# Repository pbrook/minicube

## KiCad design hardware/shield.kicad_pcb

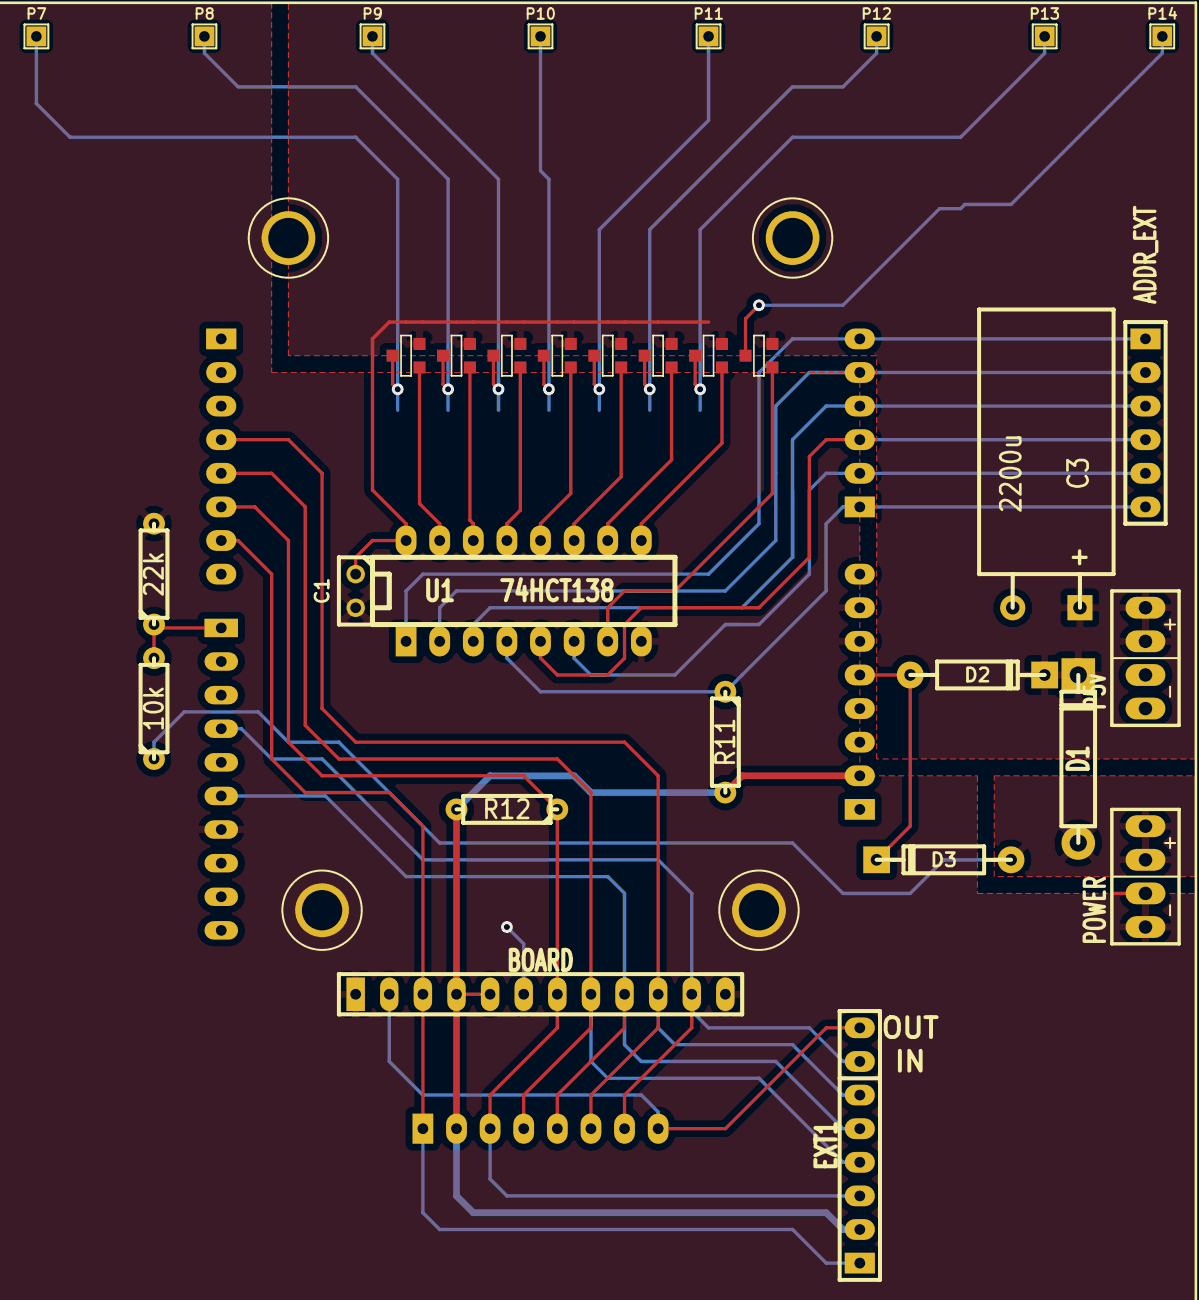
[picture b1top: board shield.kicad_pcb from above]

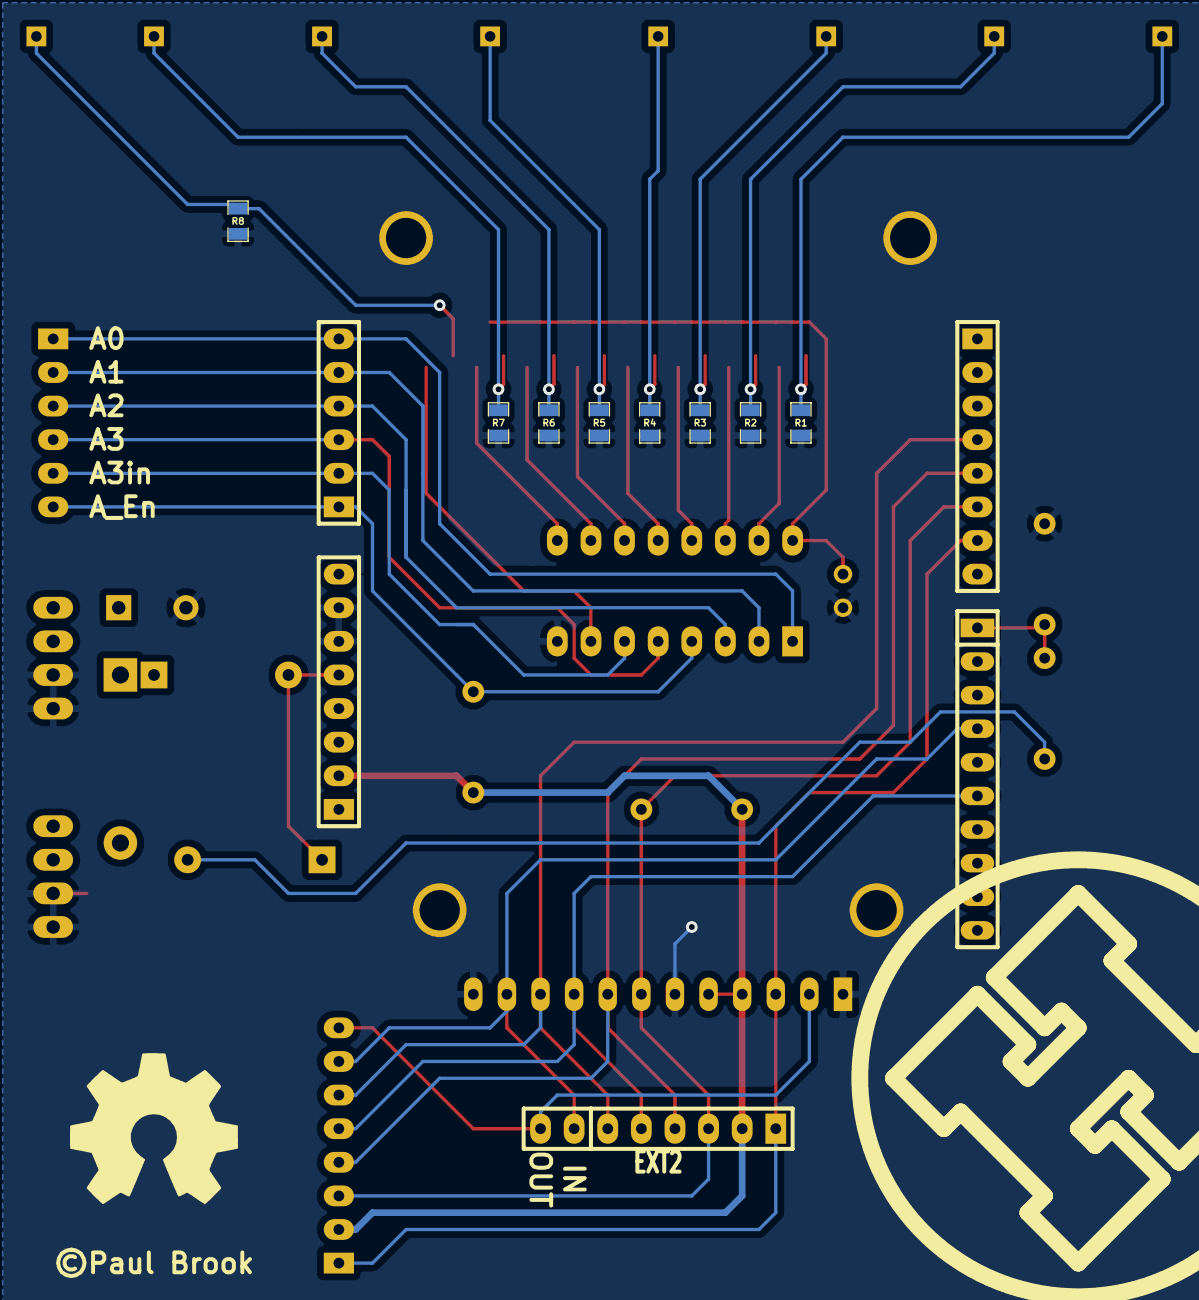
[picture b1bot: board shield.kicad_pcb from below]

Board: 2 copper layers, 49 parts (14 on the bottom side), 35 nets.

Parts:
C1: 100n; C1
C3: 2200u; CPR10X20
D1: DIODESCH; D5
D2: DIODESCH; DO-41
D3: DIODE; DO-41
HACKSPACE_LOGO: VAL**; HACKSPACE_LOGO
P1: D0_7; SIL-8-ELL
P2: D8_13; SIL-10-ELL
P3: POWER; SIL-8-ELL
P4: A0_5; SIL-6-ELL
P5: POWER; power2
P6: BOARD; SIL-12-ELL
P7, P8, P9, P10, P11, P12, P13, P14: CONN_1; SIL-1
P15, P16, P17, P18: CONN_1; HOLE3
P19: P5v; power2
P20: EXT1; SIL-8-ELL
P21: ADDR_EXT; SIL-6-ELL
P22: EXT2; SIL-8-ELL
Q1, Q2, Q3, Q4, Q5, Q6, Q7, Q8: MOS_P; SOT23GDS_NP
R1, R2, R3, R4, R5, R6, R7, R8: R; 0805
R9: 10k; R3-LARGE_PADS
R10: 22k; R3-LARGE_PADS
R11, R12: R; R3-LARGE_PADS
U1: 74HCT138; DIP-16__300_ELL

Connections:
/5v: C1.1, C3.1, D1.2, D2.2, P19.2, Q1.S, Q2.S, Q3.S, Q4.S, Q5.S, Q6.S, Q7.S, Q8.S, U1.16
/5v_EXT: D1.1, D3.1, P5.2, R9.1
/5v_USB: D2.1, D3.2, P3.5
/A0: P4.6, P21.1, U1.1
/A1: P4.5, P21.2, U1.2
/A2: P4.4, P21.3, U1.3
/A3: P4.3, P21.4, U1.5
/A3in: P4.2, P21.5, U1.6
/A_EN: P4.1, P21.6, R11.1, U1.4
/BLANK: P1.6, P6.7, P20.3, P22.3, R12.1
/GND: C1.2, C3.2, P2.7, P3.6, P3.7, P5.1, P6.1, P6.6, P6.12, P15.1, P16.1, P17.1, P18.1, P19.1, R1.2, R2.2, R3.2, R4.2, R5.2, R6.2, R7.2, R8.2, R10.2, U1.8
/GSCLK: P1.7, P6.3, P20.1, P22.1
/MODE: P1.4, P6.10, P20.6, P22.6
/Q1: Q1.G, U1.15
/Q2: Q2.G, U1.14
/Q3: Q3.G, U1.13
/Q4: Q4.G, U1.12
/Q5: Q5.G, U1.11
/Q6: Q6.G, U1.10
/Q7: Q7.G, U1.9
/Q8: Q8.G, U1.7
/S1: P7.1, Q1.D, R1.1
/S2: P8.1, Q2.D, R2.1
/S3: P9.1, Q3.D, R3.1
/S4: P10.1, Q4.D, R4.1
/S5: P11.1, Q5.D, R5.1
/S6: P12.1, Q6.D, R6.1
/S7: P13.1, Q7.D, R7.1
/S8: P14.1, Q8.D, R8.1
/SCLK: P2.6, P6.9, P20.5, P22.5
/SENSE_EXT: P2.1, R9.2, R10.1
/SIN: P2.4, P6.11, P20.7, P22.7
/SOUT: P6.2, P20.8, P22.8
/VCC: P3.2, P6.4, P6.5, P20.2, P22.2, R11.2, R12.2
/XLAT: P1.5, P6.8, P20.4, P22.4

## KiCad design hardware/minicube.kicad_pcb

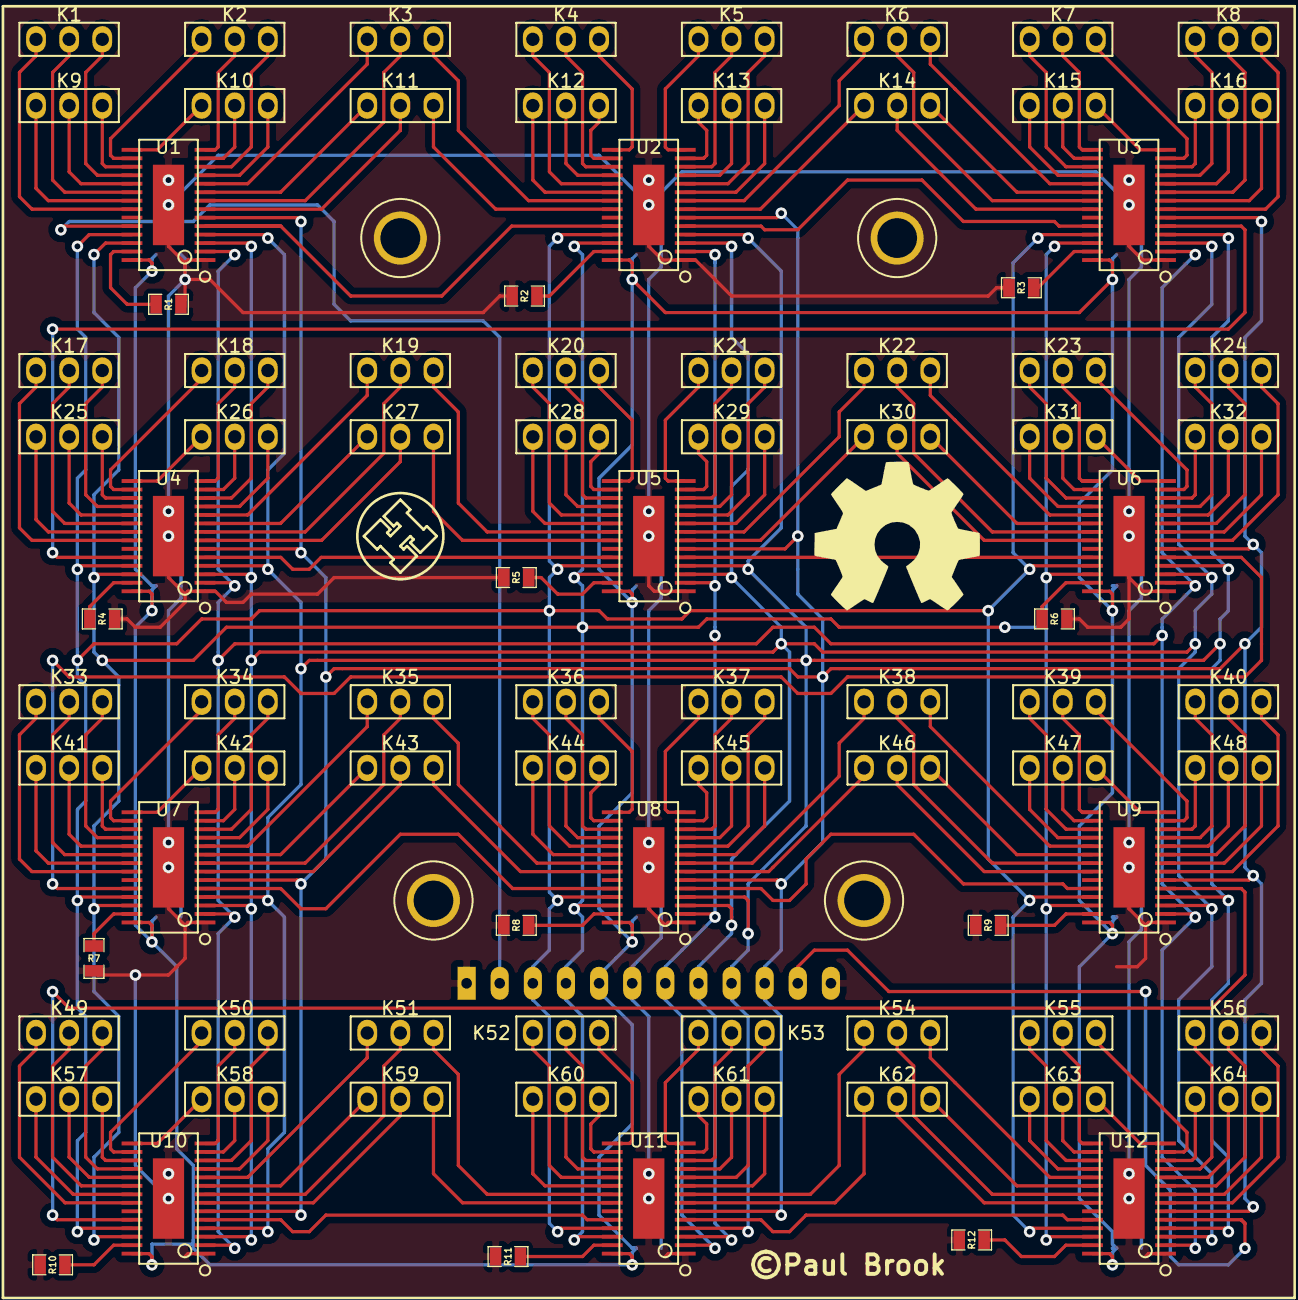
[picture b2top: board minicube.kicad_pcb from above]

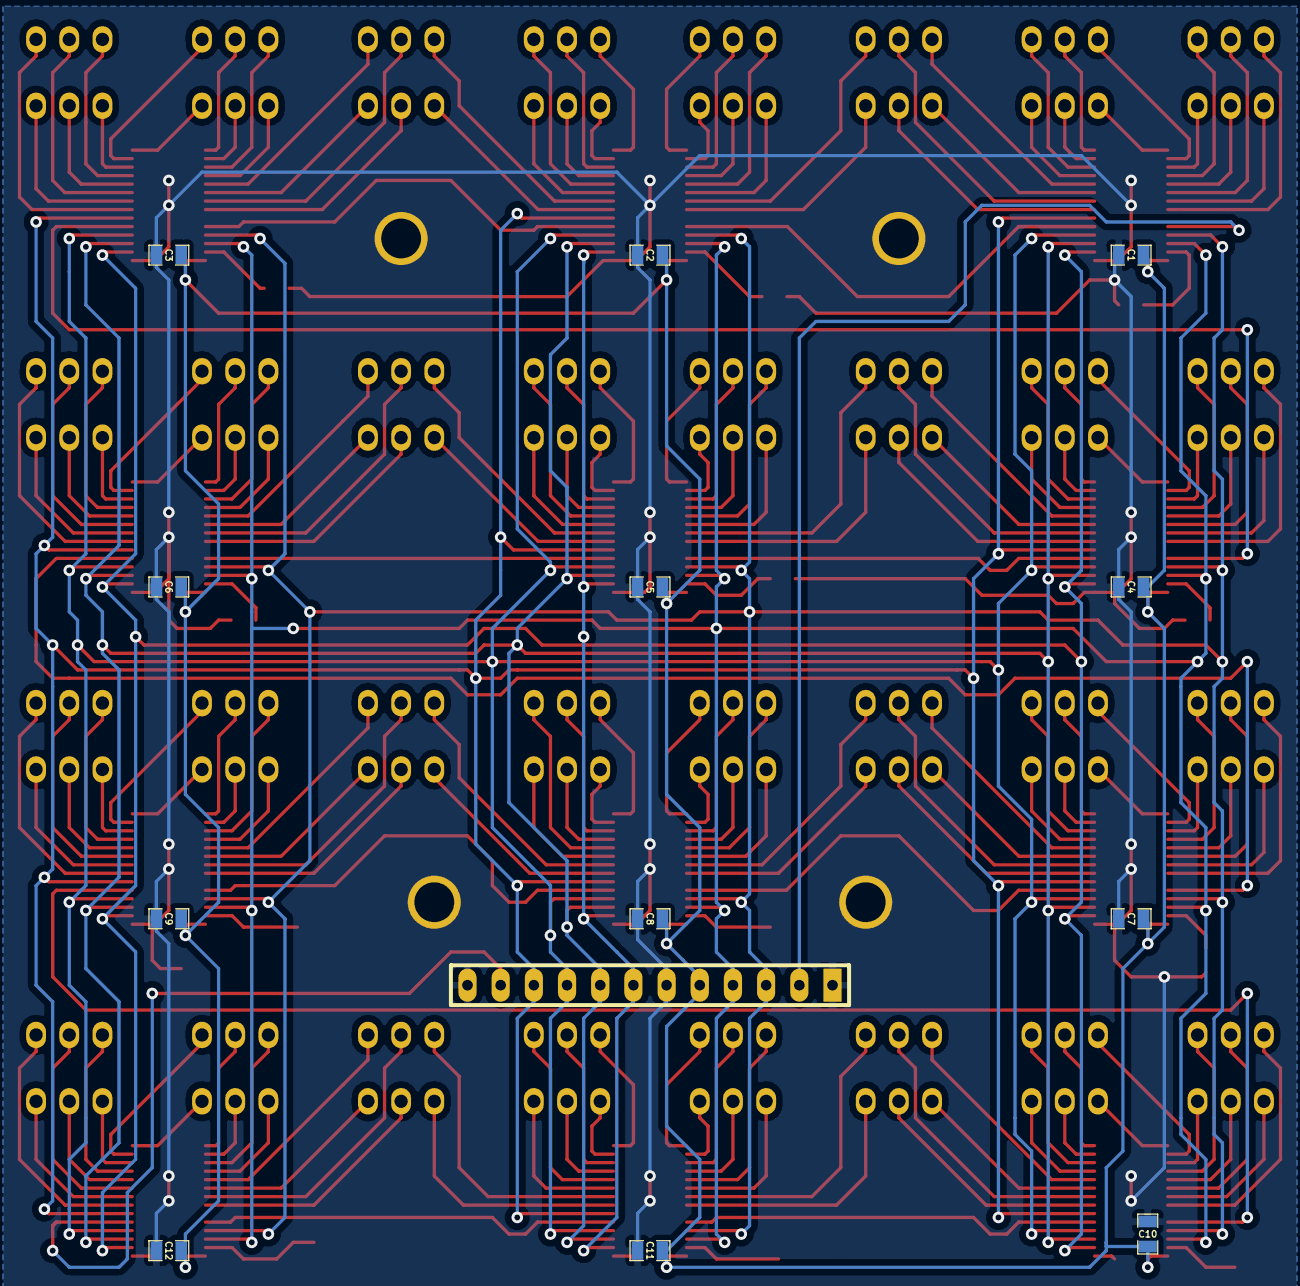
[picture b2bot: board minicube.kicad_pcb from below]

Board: 2 copper layers, 106 parts (13 on the bottom side), 225 nets.

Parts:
C1, C2, C3, C4, C5, C6, C7, C8, C9, C10, C11, C12: 100n; 0805
H1, H2, H3, H4: CONN_1; HOLE3
K1, K2, K3, K4, K5, K6, K7, K8, K9, K10, K11, K12, K13, K14, K15, K16, K17, K18, K19, K20, K21, K22, K23, K24, K25, K26, K27, K28, K29, K30, K31, K32, K33, K34, K35, K36, K37, K38, K39, K40, K41, K42, K43, K44, K45, K46, K47, K48, K49, K50, K51, K52, K53, K54, K55, K56, K57, K58, K59, K60, K61, K62, K63, K64: CONN_3; CATHODE3
LOGO_SMALL: VAL**; LOGO_SMALL
P1: CONN_12; SIL-12-ELL
R1, R2, R3, R4, R5, R6, R7, R8, R9, R10, R11, R12: R; 0805
U1, U2, U3, U4, U5, U6, U7, U8, U9, U10, U11, U12: TLC5940-PWP; HTSSOP-28

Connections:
/B1: K1.3, U1.18
/B2: K2.3, U1.12
/B3: K3.3, U2.21
/B4: K4.3, U2.15
/B5: K5.3, U2.10
/B6: K6.3, U3.19
/B7: K7.3, U3.13
/B8: K8.3, U3.7
/B9: K9.3, U1.17
/B10: K10.3, U1.11
/B11: K11.3, U2.22
/B12: K12.3, U2.16
/B13: K13.3, U2.9
/B14: K14.3, U3.20
/B15: K15.3, U3.14
/B16: K16.3, U3.8
/B17: K17.3, U4.18
/B18: K18.3, U4.12
/B19: K19.3, U5.21
/B20: K20.3, U5.15
/B21: K21.3, U5.10
/B22: K22.3, U6.19
/B23: K23.3, U6.13
/B24: K24.3, U6.7
/B25: K25.3, U4.17
/B26: K26.3, U4.11
/B27: K27.3, U5.22
/B28: K28.3, U5.16
/B29: K29.3, U5.9
/B30: K30.3, U6.20
/B31: K31.3, U6.14
/B32: K32.3, U6.8
/B33: K33.3, U7.18
/B34: K34.3, U7.12
/B35: K35.3, U8.21
/B36: K36.3, U8.15
/B37: K37.3, U8.10
/B38: K38.3, U9.19
/B39: K39.3, U9.13
/B40: K40.3, U9.7
/B41: K41.3, U7.17
/B42: K42.3, U7.11
/B43: K43.3, U8.22
/B44: K44.3, U8.16
/B45: K45.3, U8.9
/B46: K46.3, U9.20
/B47: K47.3, U9.14
/B48: K48.3, U9.8
/B49: K49.3, U10.18
/B50: K50.3, U10.12
/B51: K51.3, U11.21
/B52: K52.3, U11.15
/B53: K53.3, U11.10
/B54: K54.3, U12.19
/B55: K55.3, U12.13
/B56: K56.3, U12.7
/B57: K57.3, U10.17
/B58: K58.3, U10.11
/B59: K59.3, U11.22
/B60: K60.3, U11.16
/B61: K61.3, U11.9
/B62: K62.3, U12.20
/B63: K63.3, U12.14
/B64: K64.3, U12.8
/BLANK: P1.7, U1.2, U2.2, U3.2, U4.2, U5.2, U6.2, U7.2, U8.2, U9.2, U10.2, U11.2, U12.2
/DCPRG: P1.4, U1.26, U2.26, U3.26, U4.26, U5.26, U6.26, U7.26, U8.26, U9.26, U10.26, U11.26, U12.26
/G1: K1.2, U1.20
/G2: K2.2, U1.14
/G3: K3.2, U1.8
/G4: K4.2, U2.17
/G5: K5.2, U2.12
/G6: K6.2, U3.21
/G7: K7.2, U3.15
/G8: K8.2, U3.9
/G9: K9.2, U1.19
/G10: K10.2, U1.13
/G11: K11.2, U1.7
/G12: K12.2, U2.18
/G13: K13.2, U2.11
/G14: K14.2, U3.22
/G15: K15.2, U3.16
/G16: K16.2, U3.10
/G17: K17.2, U4.20
/G18: K18.2, U4.14
/G19: K19.2, U4.8
/G20: K20.2, U5.17
/G21: K21.2, U5.12
/G22: K22.2, U6.21
/G23: K23.2, U6.15
/G24: K24.2, U6.9
/G25: K25.2, U4.19
/G26: K26.2, U4.13
/G27: K27.2, U4.7
/G28: K28.2, U5.18
/G29: K29.2, U5.11
/G30: K30.2, U6.22
/G31: K31.2, U6.16
/G32: K32.2, U6.10
/G33: K33.2, U7.20
/G34: K34.2, U7.14
/G35: K35.2, U7.8
/G36: K36.2, U8.17
/G37: K37.2, U8.12
/G38: K38.2, U9.21
/G39: K39.2, U9.15
/G40: K40.2, U9.9
/G41: K41.2, U7.19
/G42: K42.2, U7.13
/G43: K43.2, U7.7
/G44: K44.2, U8.18
/G45: K45.2, U8.11
/G46: K46.2, U9.22
/G47: K47.2, U9.16
/G48: K48.2, U9.10
/G49: K49.2, U10.20
/G50: K50.2, U10.14
/G51: K51.2, U10.8
/G52: K52.2, U11.17
/G53: K53.2, U11.12
/G54: K54.2, U12.21
/G55: K55.2, U12.15
/G56: K56.2, U12.9
/G57: K57.2, U10.19
/G58: K58.2, U10.13
/G59: K59.2, U10.7
/G60: K60.2, U11.18
/G61: K61.2, U11.11
/G62: K62.2, U12.22
/G63: K63.2, U12.16
/G64: K64.2, U12.10
/GND: C1.2, C2.2, C3.2, C4.2, C5.2, C6.2, C7.2, C8.2, C9.2, C10.2, C11.2, C12.2, H1.1, H2.1, H3.1, H4.1, P1.1, P1.6, P1.12, R1.2, R2.2, R3.2, R4.2, R5.2, R6.2, R7.2, R8.2, R9.2, R10.2, R11.2, R12.2, U1.1, U1.29, U2.1, U2.29, U3.1, U3.29, U4.1, U4.29, U5.1, U5.29, U6.1, U6.29, U7.1, U7.29, U8.1, U8.29, U9.1, U9.29, U10.1, U10.29, U11.1, U11.29, U12.1, U12.29
/GSCLK: P1.3, U1.25, U2.25, U3.25, U4.25, U5.25, U6.25, U7.25, U8.25, U9.25, U10.25, U11.25, U12.25
/IREF1: R1.1, U1.27
/IREF2: R2.1, U2.27
/IREF3: R3.1, U3.27
/IREF4: R4.1, U4.27
/IREF5: R5.1, U5.27
/IREF6: R6.1, U6.27
/IREF7: R7.1, U7.27
/IREF8: R8.1, U8.27
/IREF9: R9.1, U9.27
/IREF10: R10.1, U10.27
/IREF11: R11.1, U11.27
/IREF12: R12.1, U12.27
/R1: K1.1, U1.22
/R2: K2.1, U1.16
/R3: K3.1, U1.10
/R4: K4.1, U2.19
/R5: K5.1, U2.14
/R6: K6.1, U2.8
/R7: K7.1, U3.17
/R8: K8.1, U3.11
/R9: K9.1, U1.21
/R10: K10.1, U1.15
/R11: K11.1, U1.9
/R12: K12.1, U2.20
/R13: K13.1, U2.13
/R14: K14.1, U2.7
/R15: K15.1, U3.18
/R16: K16.1, U3.12
/R17: K17.1, U4.22
/R18: K18.1, U4.16
/R19: K19.1, U4.10
/R20: K20.1, U5.19
/R21: K21.1, U5.14
/R22: K22.1, U5.8
/R23: K23.1, U6.17
/R24: K24.1, U6.11
/R25: K25.1, U4.21
/R26: K26.1, U4.15
/R27: K27.1, U4.9
/R28: K28.1, U5.20
/R29: K29.1, U5.13
/R30: K30.1, U5.7
/R31: K31.1, U6.18
/R32: K32.1, U6.12
/R33: K33.1, U7.22
/R34: K34.1, U7.16
/R35: K35.1, U7.10
/R36: K36.1, U8.19
/R37: K37.1, U8.14
/R38: K38.1, U8.8
/R39: K39.1, U9.17
/R40: K40.1, U9.11
/R41: K41.1, U7.21
/R42: K42.1, U7.15
/R43: K43.1, U7.9
/R44: K44.1, U8.20
/R45: K45.1, U8.13
/R46: K46.1, U8.7
/R47: K47.1, U9.18
/R48: K48.1, U9.12
/R49: K49.1, U10.22
/R50: K50.1, U10.16
/R51: K51.1, U10.10
/R52: K52.1, U11.19
/R53: K53.1, U11.14
/R54: K54.1, U11.8
/R55: K55.1, U12.17
/R56: K56.1, U12.11
/R57: K57.1, U10.21
/R58: K58.1, U10.15
/R59: K59.1, U10.9
/R60: K60.1, U11.20
/R61: K61.1, U11.13
/R62: K62.1, U11.7
/R63: K63.1, U12.18
/R64: K64.1, U12.12
/SCLK: P1.9, U1.4, U2.4, U3.4, U4.4, U5.4, U6.4, U7.4, U8.4, U9.4, U10.4, U11.4, U12.4
/SDATA1: U1.5, U2.24
/SDATA2: U2.5, U3.24
/SDATA3: U3.5, U4.24
/SDATA4: U4.5, U5.24
/SDATA5: U5.5, U6.24
/SDATA6: U6.5, U7.24
/SDATA7: U7.5, U8.24
/SDATA8: U8.5, U9.24
/SDATA9: U9.5, U10.24
/SDATA10: U10.5, U11.24
/SDATA11: U11.5, U12.24
/SIN: P1.11, U12.5
/SOUT: P1.2, U1.24
/VCC: C1.1, C2.1, C3.1, C4.1, C5.1, C6.1, C7.1, C8.1, C9.1, C10.1, C11.1, C12.1, P1.5, U1.28, U2.28, U3.28, U4.28, U5.28, U6.28, U7.28, U8.28, U9.28, U10.28, U11.28, U12.28
/VPRG: P1.10, U1.6, U2.6, U3.6, U4.6, U5.6, U6.6, U7.6, U8.6, U9.6, U10.6, U11.6, U12.6
/XLAT: P1.8, U1.3, U2.3, U3.3, U4.3, U5.3, U6.3, U7.3, U8.3, U9.3, U10.3, U11.3, U12.3

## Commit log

2015-08-29 Fix off by one error.
2015-09-05 Fix anode mosfet orientation
2015-10-11 Ignore gerbers directory
2015-10-11 Add firmware
2015-10-11 Add mbed build instructions
2015-10-11 Remove unused code.

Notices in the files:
hardware/minicube.kicad_pcb:
©Paul Brook
